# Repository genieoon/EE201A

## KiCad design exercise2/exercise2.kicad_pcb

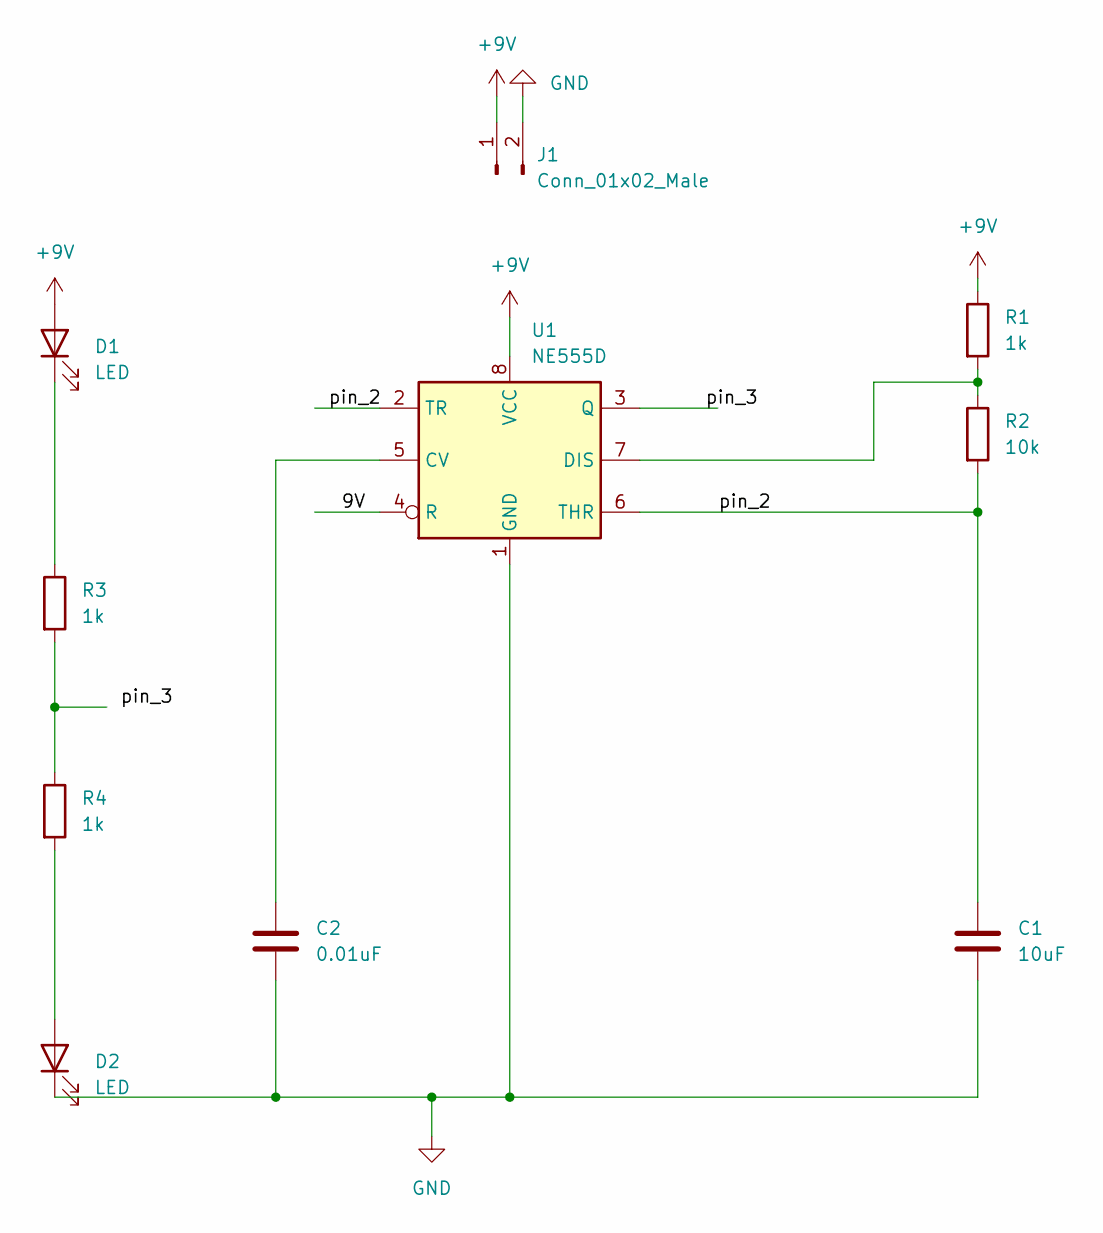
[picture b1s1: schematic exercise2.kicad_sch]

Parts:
C1: 10uF; CP_EIA-3216-18_Kemet-A_Pad1.58x1.35mm_HandSolder
C2: 0.01uF; C_0805_2012Metric_Pad1.18x1.45mm_HandSolder
D1, D2: LED; LED_1206_3216Metric_Pad1.42x1.75mm_HandSolder
J1: Conn_01x02_Male; TerminalBlock_bornier-2_P5.08mm
R1, R3, R4: 1k; R_0805_2012Metric_Pad1.20x1.40mm_HandSolder
R2: 10k; R_0805_2012Metric_Pad1.20x1.40mm_HandSolder
U1: NE555D; SOIC-8_3.9x4.9mm_P1.27mm

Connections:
+9V: D1.2 (A), J1.1, R1.1, U1.8 (VCC)
/9V: U1.4 (R)
/pin_2: C1.1, R2.2, U1.2 (TR), U1.6 (THR)
/pin_3: U1.3 (Q)
GND: C1.2, C2.2, D2.1 (K), J1.2, U1.1 (GND)
unnamed: C2.1, U1.5 (CV)
unnamed: D1.1 (K), R3.1
unnamed: D2.2 (A), R4.2
unnamed: R1.2, R2.1, U1.7 (DIS)
unnamed: R3.2, R4.1

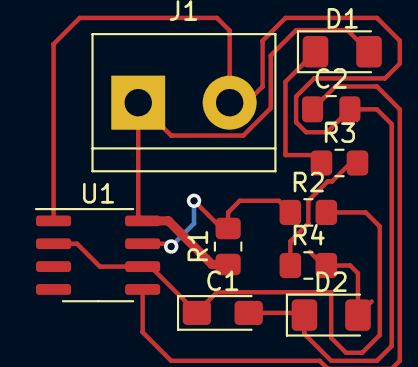
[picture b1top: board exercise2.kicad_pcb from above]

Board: 2 copper layers, 10 parts (0 on the bottom side), 8 nets.

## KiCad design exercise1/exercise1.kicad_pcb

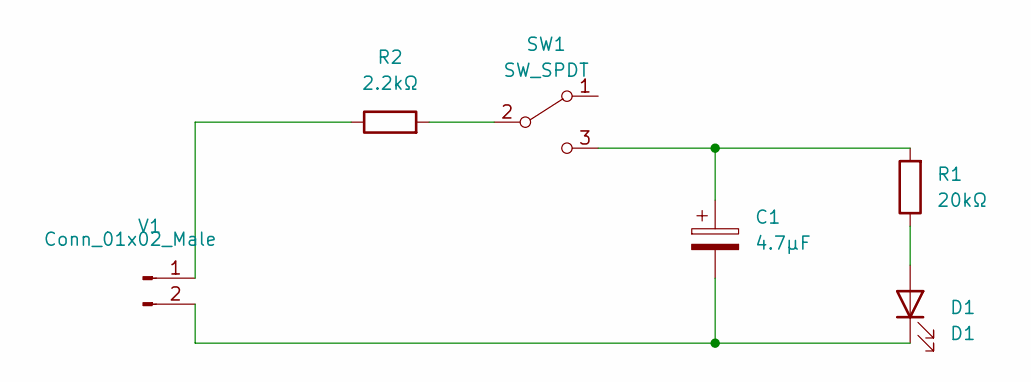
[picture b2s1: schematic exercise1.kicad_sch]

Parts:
C1: 4.7µF; C_Radial_D5.0mm_H5.0mm_P2.00mm
D1: D1; LED_D5.0mm
R1: 20kΩ; R_Axial_DIN0516_L15.5mm_D5.0mm_P20.32mm_Horizontal
R2: 2.2kΩ; R_Axial_DIN0516_L15.5mm_D5.0mm_P20.32mm_Horizontal
SW1: SW_SPDT; SW_E-Switch_EG1224_SPDT_Angled
V1: Conn_01x02_Male; JST_PH_B2B-PH-K_1x02_P2.00mm_Vertical

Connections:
unnamed: C1.1, R1.2, SW1.3 (C)
unnamed: C1.2, D1.1 (K), V1.2
unnamed: D1.2 (A), R1.1
unnamed: R2.1, V1.1
unnamed: R2.2, SW1.2 (B)

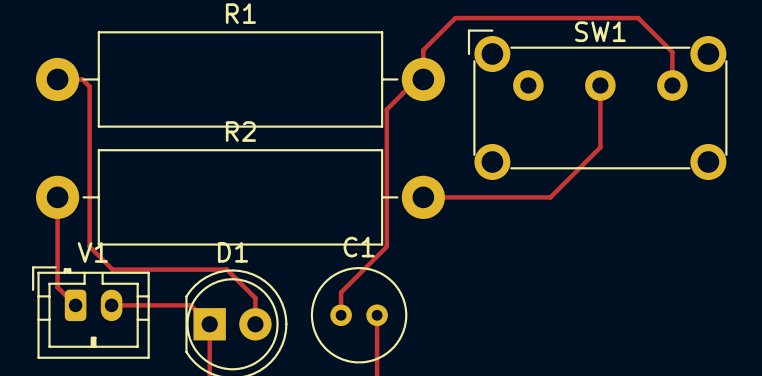
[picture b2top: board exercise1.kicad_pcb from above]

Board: 2 copper layers, 6 parts (0 on the bottom side), 5 nets.

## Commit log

2023-01-10 Adding README
2023-01-10 merged Lab2
2023-01-10 testing
2023-01-17 Adding Exercise 2
2023-01-18 Adding Exercise 4
2023-01-24 Lab4 Exercise1
